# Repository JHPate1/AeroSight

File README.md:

# AeroSight
### An Open-Source, Low-Cost Retroreflective Schlieren Imaging System

## Overview
AeroSight is a high-fidelity Schlieren imaging device built to make advanced aerodynamic and thermodynamic visualization actually accessible. Professional-grade Schlieren setups, the kind NASA uses easily runs past $5,000. AeroSight delivers 1080p visualization for a fraction of that, using a modular optical design and open-source hardware. Swap lenses, swap beam splitters, tweak the software. The whole thing is built for people who want to experiment like real lab equipment.

## How it looks inside
(Lost Media)
Guide:
Yellow-Enclosure
Blue-Lens Holder
Grey-Cam Holder
Orange-LED Holder
Red-BeamSplitter
## Why AeroSight?
* **Cheap where it counts:** Total build cost is about $514.
* **Modular:** Upgrade optics (lens, NPBS cube) as your needs change.
* **Flexible software:** Raw video, real-color rendering, custom gradient mapping, all the good stuff.

## Project Contents
```/PCB/``` PCB files
```3D ``` 3D Printed Files

## Bill of Materials (BOM)

| Category | Item | Quantity | Total |
| :--- | :--- | :--- | :--- |
| **Processing** | Waveshare ESP32-P4-WIFI6 Development Board | 1 | $24.99 |
| **Camera** | Arducam OV5647 5MP Camera (CS Mount) | 1 | $25.99 |
| **Camera Cable** | Raspberry Pi CSI Ribbon Cable | 1 | $4.99 |
| **Optics** | 25 mm 50:50 Beam Splitter Cube | 1 | $94.95 |
| **Optics** | Eisco Plano-Convex Lens (50mm) | 2 | $19.98 |
| **Optics** | Front Surface Mirror 5.5" x 8" | 1 | $12.98 |
| **Illumination** | 3 W 3535 High-Power White LED | 1 | $10.29 |
| **Cooling** | 30 mm 5 V Brushless Fan Kit | 1 | $9.99 |
| **Cooling** | 20x20x10 mm Aluminum Heatsink | 1 | $7.99 |
| **Thermal** | ARCTIC MX-7 Thermal Paste | 1 | $6.89 |
| **Mechanical** | Metric Screw/Nut/Washer Kit | 1 | $13.98 |
| **Electrical** | 28 AWG Silicone Wire | 1 | $10.82 |
| **Electrical** | SPST Rocker Switch Kit | 1 | $8.99 |
| **Audio** | 3 W 8 Ω Mini Speaker | 1 | $9.99 |
| **Assembly** | WEP 946D IV Mini Reflow Hot Plate | 1 | $28.79 |
| **PCBWay** | PCB Fabrication & 3D Printing | 1 | $163.50 |
| **Shipping/Tax**| Combined Est. Tax/Shipping/Tariffs | - | $58.88 |
| **---** | **GRAND TOTAL** | --- | **$514.00** |

---

## Customization & Notes
* **Modular optics:** The optical path is built to swap. Change the primary lens or NPBS cube depending on your field of view or light sensitivity needs.
* **Fabrication:** The 3D-printed enclosure eats a big chunk of the budget. If you have access to a printer in-house, you can knock about $126.50 off the total.

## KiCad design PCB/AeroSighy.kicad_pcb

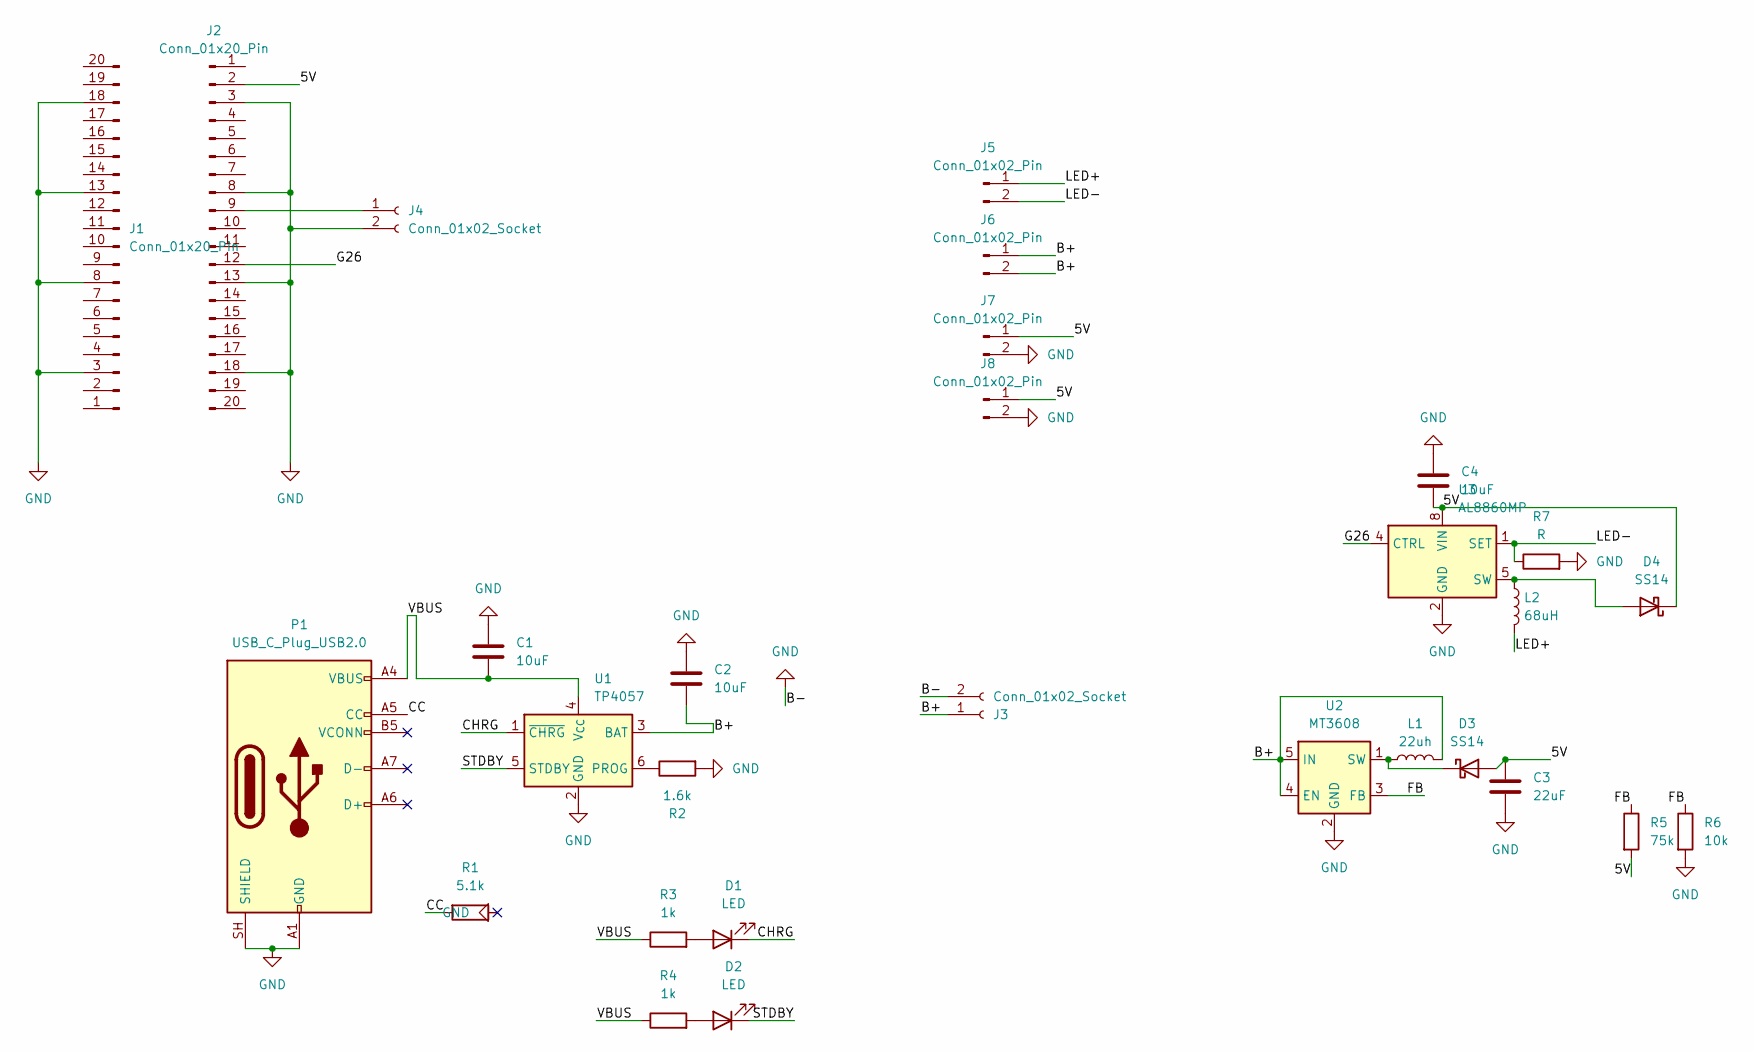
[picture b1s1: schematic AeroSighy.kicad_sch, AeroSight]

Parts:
C1, C2, C4: 10uF; C_0504_1310Metric
C3: 22uF; C_0504_1310Metric
D1, D2: LED; LED_0805_2012Metric
D3, D4: SS14; D_SMA
J1, J2: Conn_01x20_Pin; PinSocket_1x20_P2.54mm_Vertical
J3, J4: Conn_01x02_Socket; PinHeader_1x02_P2.54mm_Vertical
J5: Conn_01x02_Pin; PinSocket_1x02_P2.00mm_Vertical
J6, J7, J8: Conn_01x02_Pin; PinSocket_1x02_P2.54mm_Vertical
L1: 22uh; L_0805_2012Metric
L2: 68uH; L_0805_2012Metric
P1: USB_C_Plug_USB2.0; USB_C_Receptacle_Amphenol_12401948E412A
R1: 5.1k; R_0603_1608Metric
R2: 1.6k; R_0603_1608Metric
R3, R4: 1k; R_0603_1608Metric
R5: 75k; R_0603_1608Metric
R6: 10k; R_0603_1608Metric
R7: R; R_0603_1608Metric
U1: TP4057; TSOT-23-6
U2: MT3608; SOT-23-6
U3: AL8860MP; MSOP-8-1EP_3x3mm_P0.65mm_EP1.5x1.8mm

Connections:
/5V: C3.1, C4.2, D3.2 (A), D4.1 (K), J2.2, J7.1, J8.1, R5.2, U3.8 (VIN)
/B+: C2.2, J3.1, J6.1, J6.2, L1.2, U1.3 (BAT), U2.4 (EN), U2.5 (IN)
/CC: P1.A5 (CC), R1.2
/CHRG: D1.1 (K), U1.1 (~CHRG)
/FB: R5.1, R6.1, U2.3 (FB)
/G26: J2.12, U3.4 (CTRL)
/LED+: J5.1, L2.2
/LED-: J5.2, R7.1, U3.1 (SET)
/STDBY: D2.1 (K), U1.5 (STDBY)
/VBUS: C1.2, P1.A4 (VBUS), P1.A9 (VBUS), P1.B4 (VBUS), P1.B9 (VBUS), R3.1, R4.1, U1.4 (V_{CC})
GND: C1.1, C2.1, C3.2, C4.1, J1.3, J1.8, J1.13, J1.18, J2.3, J2.8, J2.13, J2.18, J3.2, J4.2, J7.2, J8.2, P1.A1 (GND), P1.A12 (GND), P1.B1 (GND), P1.B12 (GND), P1.SH (SHIELD), R1.1, R2.2, R6.2, R7.2, U1.2 (GND), U2.2 (GND), U3.2 (GND), U3.3 (GND), U3.9 (GND)
unnamed: D1.2 (A), R3.2
unnamed: D2.2 (A), R4.2
unnamed: D3.1 (K), L1.1, U2.1 (SW)
unnamed: D4.2 (A), L2.1, U3.5 (SW), U3.6 (SW)
unnamed: J2.9, J4.1
unnamed: R2.1, U1.6 (PROG)

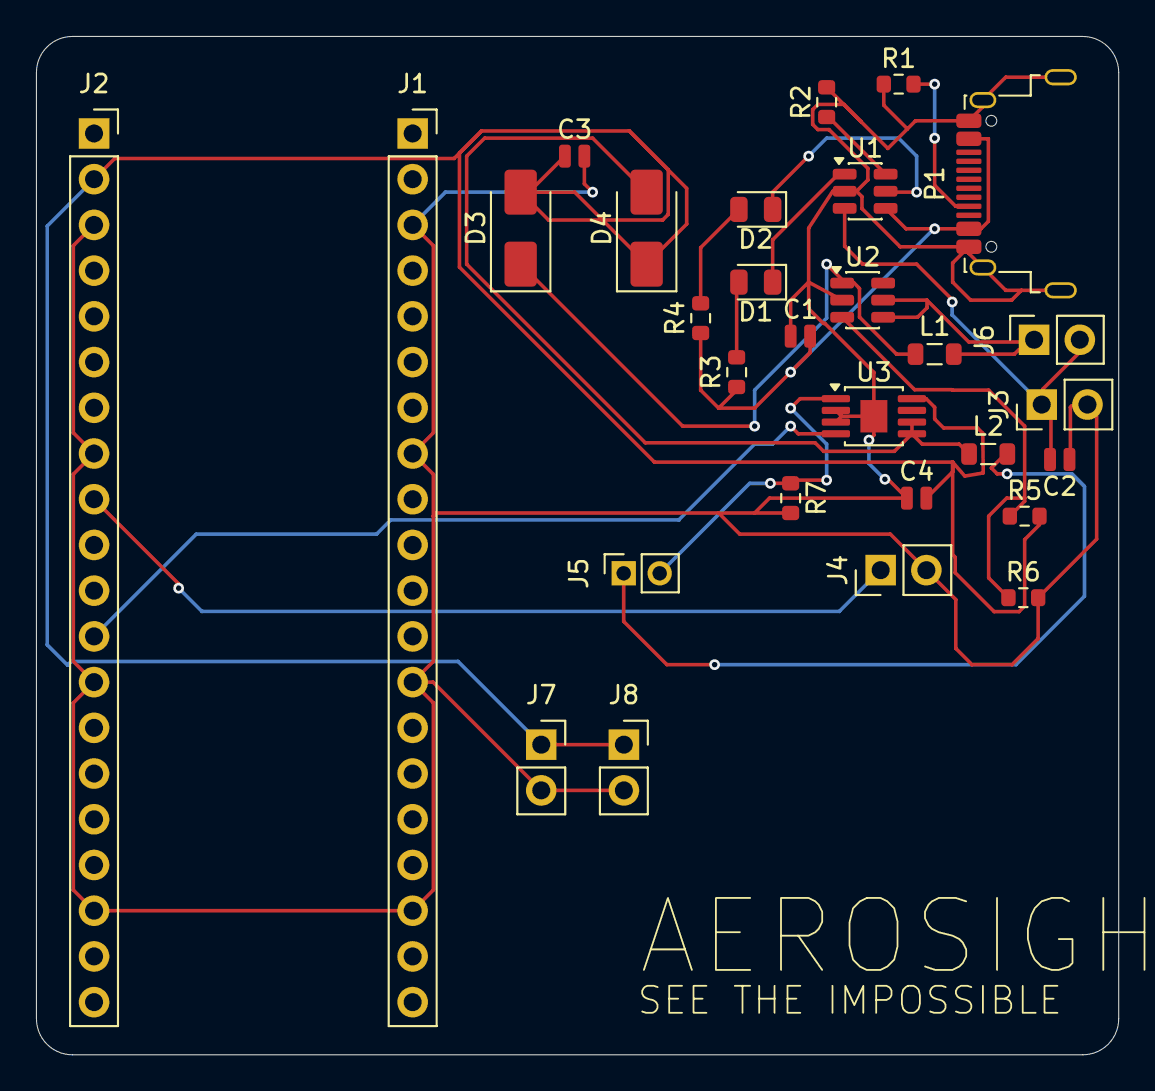
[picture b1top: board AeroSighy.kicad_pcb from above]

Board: 2 copper layers, 60.1 x 56.6 mm, 29 parts (0 on the bottom side), 17 nets.

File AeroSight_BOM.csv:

Category,Item,Description,Qty,Unit Price,Line Total,Supplier,Link,Designator,Footprint
Processing,Waveshare ESP32-P4-WIFI6,"WiFi 6 dev board, MIPI-CSI support",1,$24.99,$24.99,Amazon,https://www.amazon.com/gp/product/B0FKH4KK7M,,
Camera,Arducam OV5647 5MP,5MP CS-mount camera module,1,$25.99,$25.99,Amazon,https://www.amazon.com/gp/product/B012ETE75I,,
Camera,Raspberry Pi CSI Cable,"15-to-22 pin, 30 cm ribbon",1,$4.99,$4.99,Amazon,https://www.amazon.com/cart,,
Optics,NPBS Cube,"25 mm 50:50 non-polarizing, 400-700 nm",1,$94.95,$94.95,Labnique,https://labnique.com/products/25mm-beamsplitter-cube-non-pol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,,
Optics,Plano-Convex Lens,"50 mm dia, 50 mm focal length",2,$9.99,$19.98,Amazon,https://www.amazon.com/gp/product/B0FKHMTNPM,,
Optics,Front Surface Mirror,"5.5 in x 8 in, first-surface",1,$12.98,$12.98,Amazon,https://www.amazon.com/gp/product/B0BMJN2LVL,,
Illumination,White LED,"3W 3535, 6500-7000K",1,$10.29,$10.29,Amazon,https://www.amazon.com/gp/product/B0CL8XPX21,,
Cooling,30 mm Fan,"5V brushless, sleeve bearing",1,$9.99,$9.99,Amazon,https://www.amazon.com/gp/product/B0792BW2VH,,
Cooling,Aluminum Heatsink,"20x20x10 mm, passive",1,$7.99,$7.99,Amazon,https://www.amazon.com/gp/product/B0FPCVP3QZ,,
Thermal,ARCTIC MX-7,"Thermal paste, 4g tube",1,$6.89,$6.89,Amazon,https://www.amazon.com/gp/product/B0FT2TSY47,,
Mechanical,Hardware Kit,"M3-M6 screws, nuts, washers",1,$13.98,$13.98,Amazon,https://www.amazon.com/gp/product/B0BN297MP5,,
Electrical,Silicone Wire,"28 AWG, multi-color set",1,$10.82,$10.82,Amazon,https://www.amazon.com/gp/product/B07HGT77R5,,
Electrical,Rocker Switch,"SPST, panel mount kit",1,$8.99,$8.99,Amazon,https://www.amazon.com/gp/product/B0DLBD4X2B,,
Audio,Mini Speaker,"3W, 8 ohm",1,$9.99,$9.99,Amazon,https://www.amazon.com/gp/product/B0B4D1BN4F,,
Assembly,Mini Reflow Hot Plate,"WEP 946D IV, preheater",1,$28.79,$28.79,Amazon,https://www.amazon.com/gp/product/B0FDWNMC71,,
,,,,,,,,,
PCB Passives,Ceramic Capacitor,"10 uF, 0504 (1310 metric)",3,TBD,TBD,DigiKey/Mouser,,C1-C3,C_0504_1310Metric
PCB Passives,Ceramic Capacitor,"22 uF, 0504 (1310 metric)",1,TBD,TBD,DigiKey/Mouser,,C4,C_0504_1310Metric
PCB Passives,LED,"0805 (2012 metric), status indicator",2,TBD,TBD,DigiKey/Mouser,,D1-D2,LED_0805_2012Metric
PCB Passives,Schottky Diode,"SS14, SMA package",2,TBD,TBD,DigiKey/Mouser,,D3-D4,D_SMA
PCB Passives,Inductor,"22 uH, 0805 (2012 metric)",1,TBD,TBD,DigiKey/Mouser,,L1,L_0805_2012Metric
PCB Passives,Inductor,"68 uH, 0805 (2012 metric)",1,TBD,TBD,DigiKey/Mouser,,L2,L_0805_2012Metric
PCB Passives,Resistor,"5.1 kOhm, 0603 (1608 metric)",1,TBD,TBD,DigiKey/Mouser,,R1,R_0603_1608Metric
PCB Passives,Resistor,"1.6 kOhm, 0603 (1608 metric)",1,TBD,TBD,DigiKey/Mouser,,R2,R_0603_1608Metric
PCB Passives,Resistor,"1 kOhm, 0603 (1608 metric)",2,TBD,TBD,DigiKey/Mouser,,R3-R4,R_0603_1608Metric
PCB Passives,Resistor,"75 kOhm, 0603 (1608 metric)",1,TBD,TBD,DigiKey/Mouser,,R5,R_0603_1608Metric
PCB Passives,Resistor,"10 kOhm, 0603 (1608 metric)",1,TBD,TBD,DigiKey/Mouser,,R6,R_0603_1608Metric
PCB Passives,Resistor,"TBD value, 0603 (1608 metric)",1,TBD,TBD,DigiKey/Mouser,,R7,R_0603_1608Metric
PCB ICs,Li-Ion Charger,"TP4057, TSOT-23-6",1,TBD,TBD,LCSC/DigiKey,,U1,TSOT-23-6
PCB ICs,Boost Converter,"MT3608, SOT-23-6",1,TBD,TBD,LCSC/DigiKey,,U2,SOT-23-6
PCB ICs,LED Driver,"AL8860MP, MSOP-8-1EP",1,TBD,TBD,DigiKey/Mouser,,U3,MSOP-8-1EP_3x3mm_P0.65mm_EP1.5x1.8mm
PCB Connectors,Pin Socket,"1x20, 2.54 mm pitch, vertical",2,TBD,TBD,DigiKey/Mouser,,J1-J2,PinSocket_1x20_P2.54mm_Vertical
PCB Connectors,Pin Header,"1x02, 2.54 mm pitch, vertical",2,TBD,TBD,DigiKey/Mouser,,J3-J4,PinHeader_1x02_P2.54mm_Vertical
PCB Connectors,Pin Socket,"1x02, 2.00 mm pitch, vertical",1,TBD,TBD,DigiKey/Mouser,,J5,PinSocket_1x02_P2.00mm_Vertical
PCB Connectors,Pin Socket,"1x02, 2.54 mm pitch, vertical",3,TBD,TBD,DigiKey/Mouser,,J6-J8,PinSocket_1x02_P2.54mm_Vertical
PCB Connectors,USB-C Receptacle,"Amphenol 12401948E412A, USB 2.0",1,TBD,TBD,DigiKey/Mouser,,J9,USB_C_Receptacle_Amphenol_12401948E412A
,,,,,,,,,
Fabrication,PCB,"2-layer, custom design",1,$37.00,$37.00,PCBWay,,,
Fabrication,3D Printing,"Enclosure parts, SLA/FDM",1,$126.50,$126.50,PCBWay,,,
Shipping,Amazon Shipping + Tax,Combined estimate,1,$31.40,$31.40,Amazon,,,
Shipping,Labnique Shipping + Tax,Combined estimate,1,$9.99,$9.99,Labnique,,,
Shipping,PCBWay Taxes/Tariffs,Estimated import duties,1,$17.50,$17.50,PCBWay,,,
,,,,,,,,,
SUBTOTAL,Mechanical / Off-the-Shelf,,,,$291.61,,,,
SUBTOTAL,PCB Components,,,,TBD,,,,
SUBTOTAL,Fabrication & Shipping,,,,$222.39,,,,
,,,,,,,,,
GRAND TOTAL,,,,,$514.00 + PCB,,,,

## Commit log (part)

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2026-06-27 Create temp
2026-06-27 Revise README for AeroSight project details
    Updated the README to provide a detailed overview of the AeroSight project, including its features, project contents, bill of materials, and customization notes.
2026-06-28 Add internal view section to README
    Added a section on the internal appearance of the device with an image.
2026-06-28 Add component guide to README
    Added a guide section with color-coded components for better understanding.
